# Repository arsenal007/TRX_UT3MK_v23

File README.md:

# TRX_UT3MK_v23
MAINBOARD for UT3MK v23.01

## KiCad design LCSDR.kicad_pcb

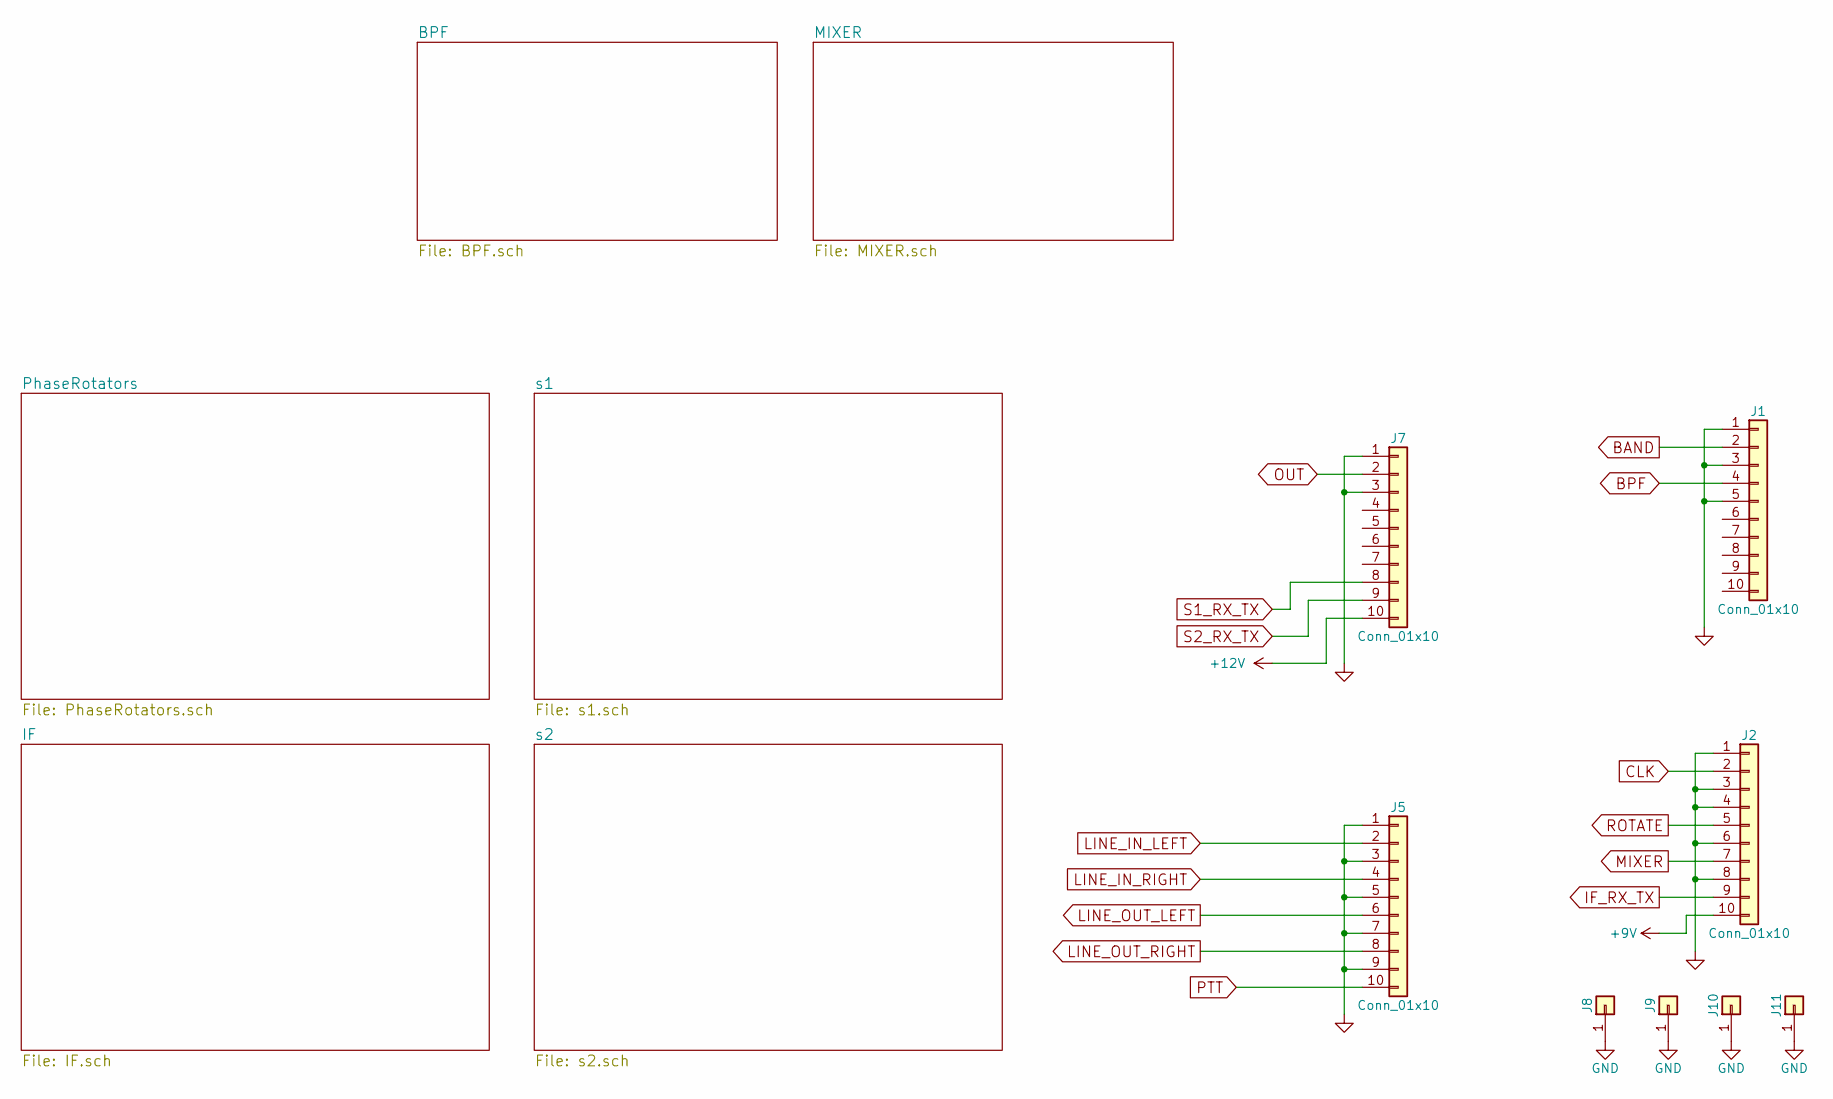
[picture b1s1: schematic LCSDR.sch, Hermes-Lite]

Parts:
J1, J2, J5, J7: Conn_01x10; Pin_Header_Straight_1x10_Pitch2.54mm
J8, J9, J10, J11: Conn_01x01; MountingHole_3.2mm_M3_DIN965_Pad

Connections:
+9V: J2.10; also elsewhere on the board
+12V: J7.10; also elsewhere on the board
BAND: J1.2; also elsewhere on the board
BPF: J1.4; also elsewhere on the board
CLK: J2.2; also elsewhere on the board
GND: J1.1, J1.3, J1.5, J2.1, J2.3, J2.4, J2.6, J2.8, J5.1, J5.3, J5.5, J5.7, J5.9, J7.1, J7.3, J8.1, J9.1, J10.1, J11.1; also elsewhere on the board
IF_RX_TX: J2.9; also elsewhere on the board
LINE_IN_LEFT: J5.2; also elsewhere on the board
LINE_IN_RIGHT: J5.4; also elsewhere on the board
LINE_OUT_LEFT: J5.6; also elsewhere on the board
LINE_OUT_RIGHT: J5.8; also elsewhere on the board
MIXER: J2.7; also elsewhere on the board
OUT: J7.2; also elsewhere on the board
PTT: J5.10; also elsewhere on the board
ROTATE: J2.5; also elsewhere on the board
S1_RX_TX: J7.8; also elsewhere on the board
S2_RX_TX: J7.9; also elsewhere on the board

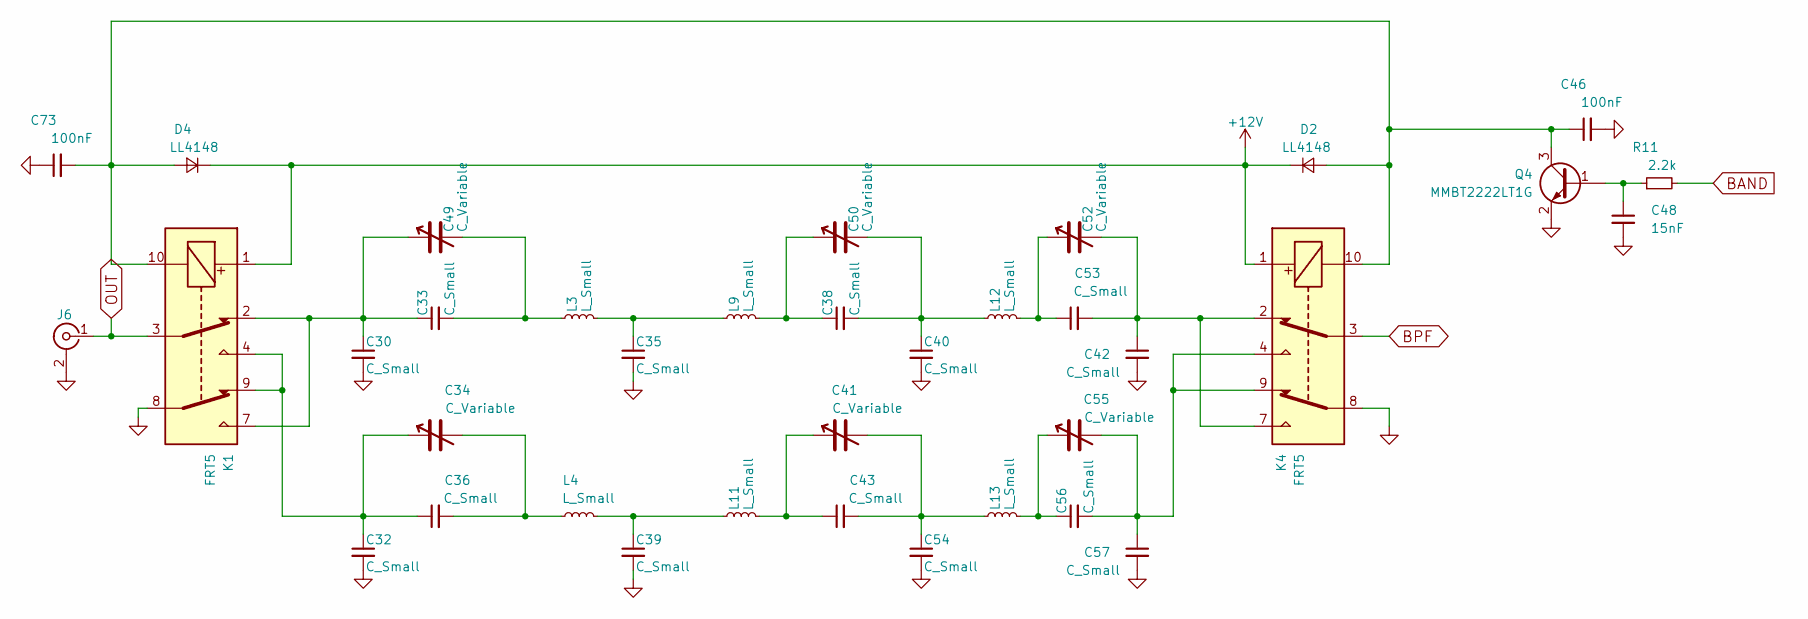
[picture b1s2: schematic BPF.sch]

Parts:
C30, C32, C33, C35, C36, C38, C39, C40, C42, C43, C53, C54, C56, C57: C_Small; C_1206_0603
C34, C41, C49, C50, C52, C55: C_Variable; C_Trimmer_Murata_TZC3
C46, C73: 100nF; C_1206_0603
C48: 15nF; C_0603_HandSoldering
D2, D4: LL4148; D_MiniMELF
J6: Conn_Coaxial; RFCONNECTOR
K1, K4: FRT5; Relay_DPDT_FRT5
L3, L4, L9, L11, L12, L13: L_Small; Choke_Toroid_6,5x13mm_Vertical
Q4: MMBT2222LT1G; SOT-23
R11: 2.2k; R_1206_0603

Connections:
+12V: D2.1 (K), D4.1 (K), K1.1, K4.1; also elsewhere on the board
BAND: R11.2; also elsewhere on the board
BPF: K4.3; also elsewhere on the board
GND: C30.2, C32.2, C35.2, C39.2, C40.2, C42.2, C46.2, C48.2, C54.2, C57.2, C73.1, J6.2 (Ext), K1.8, K4.8, Q4.2 (E); also elsewhere on the board
unnamed: C30.1, C33.1, C49.1, K1.2, K1.7
unnamed: C32.1, C34.1, C36.1, K1.4, K1.9
unnamed: C33.2, C49.2, L3.1
unnamed: C34.2, C36.2, L4.1
unnamed: C35.1, L3.2, L9.1
unnamed: C38.1, C50.1, L9.2
unnamed: C38.2, C40.1, C50.2, L12.1
unnamed: C39.1, L4.2, L11.1
unnamed: C41.1, C43.1, L11.2
unnamed: C41.2, C43.2, C54.1, L13.1
unnamed: C42.1, C52.2, C53.2, K4.2, K4.7
unnamed: C46.1, C73.2, D2.2 (A), D4.2 (A), K1.10, K4.10, Q4.3 (C)
unnamed: C48.1, Q4.1 (B), R11.1
unnamed: C52.1, C53.1, L12.2
unnamed: C55.1, C56.1, L13.2
unnamed: C55.2, C56.2, C57.1, K4.4, K4.9
OUT: J6.1 (In), K1.3; also elsewhere on the board

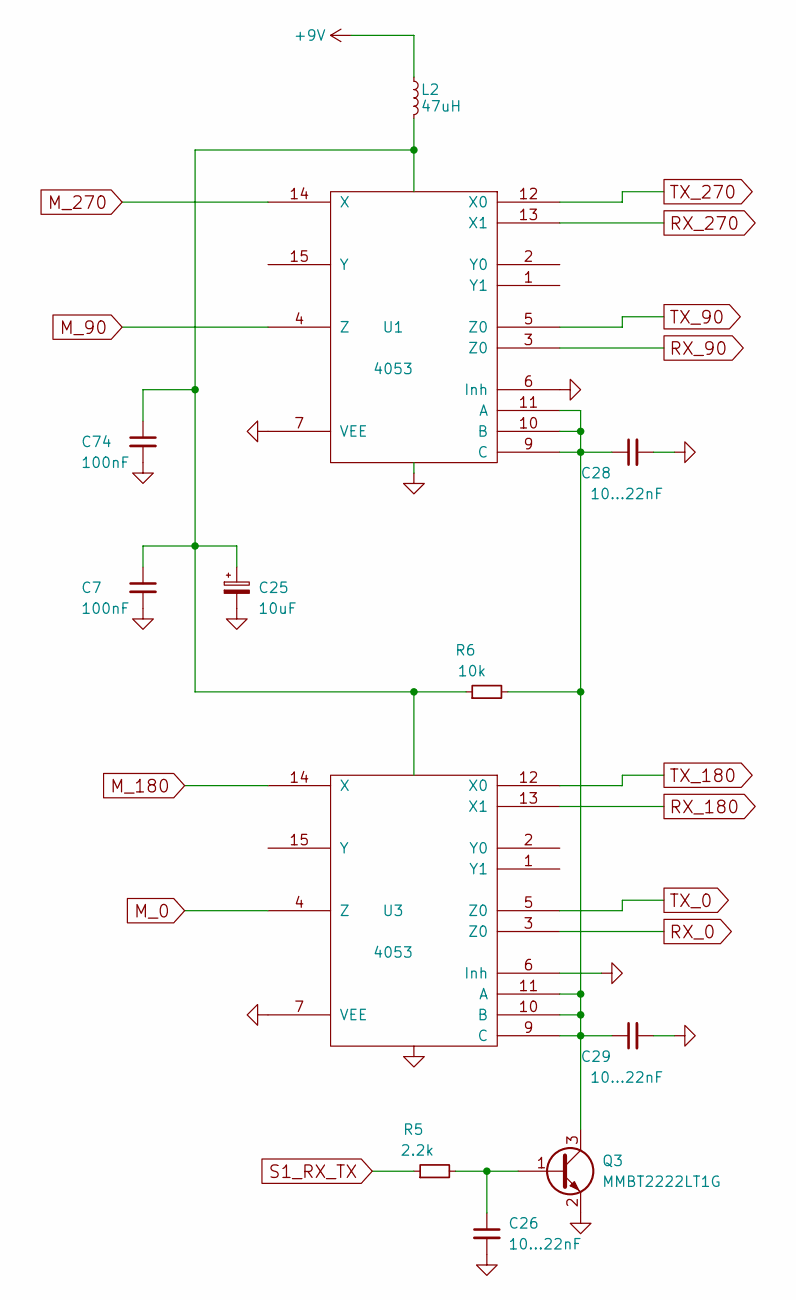
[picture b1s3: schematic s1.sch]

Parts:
C7, C74: 100nF; C_1206_0603
C25: 10uF; CP_Radial_D5.0mm_P2.00mm
C26, C28, C29: 10...22nF; C_0603_HandSoldering
L2: 47uH; Choke_Horizontal_RM10mm
Q3: MMBT2222LT1G; SOT-23
R5: 2.2k; R_1206_0603
R6: 10k; R_0603_HandSoldering
U1, U3: 4053; TSSOP-16_4.4x5mm_Pitch0.65mm

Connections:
+9V: L2.1; also elsewhere on the board
GND: C7.2, C25.2, C26.2, C28.2, C29.2, C74.2, Q3.2 (E), U1.6 (Inh), U1.7 (VEE), U1.8 (VSS), U3.6 (Inh), U3.7 (VEE), U3.8 (VSS); also elsewhere on the board
M_0: U3.4 (Z); also elsewhere on the board
M_90: U1.4 (Z); also elsewhere on the board
M_180: U3.14 (X); also elsewhere on the board
M_270: U1.14 (X); also elsewhere on the board
unnamed: C26.1, Q3.1 (B), R5.2
unnamed: C28.1, C29.1, Q3.3 (C), R6.2, U1.9 (C), U1.10 (B), U1.11 (A), U3.9 (C), U3.10 (B), U3.11 (A)
RX_0: U3.3 (Z0); also elsewhere on the board
RX_90: U1.3 (Z0); also elsewhere on the board
RX_180: U3.13 (X1); also elsewhere on the board
RX_270: U1.13 (X1); also elsewhere on the board
S1_RX_TX: R5.1; also elsewhere on the board
TX_0: U3.5 (Z0); also elsewhere on the board
TX_90: U1.5 (Z0); also elsewhere on the board
TX_180: U3.12 (X0); also elsewhere on the board
TX_270: U1.12 (X0); also elsewhere on the board
VDD: C7.1, C25.1, C74.1, L2.2, R6.1, U1.16 (VDD), U3.16 (VDD)

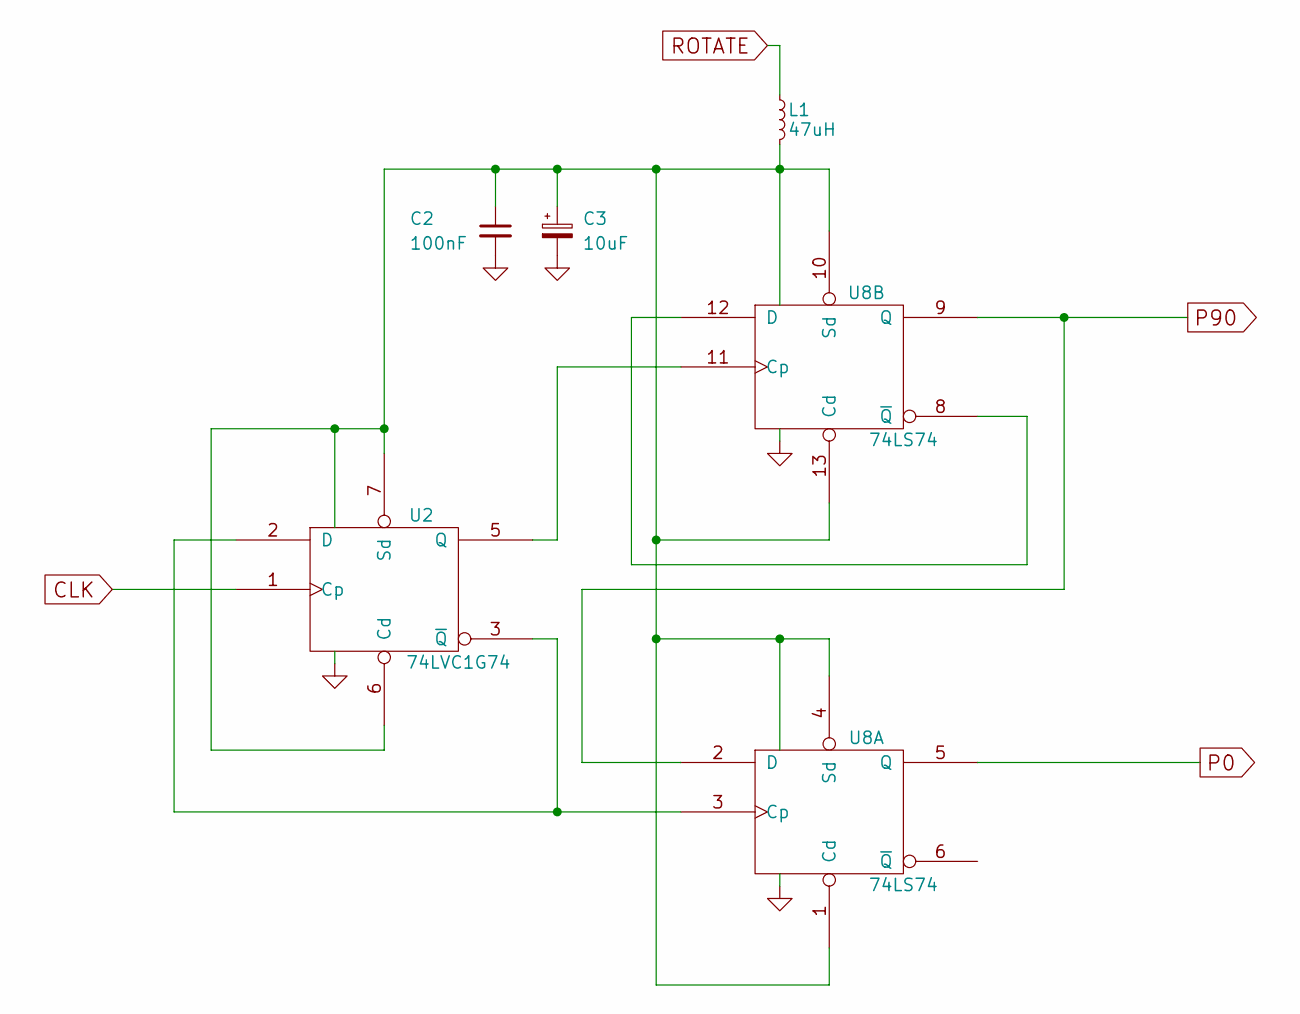
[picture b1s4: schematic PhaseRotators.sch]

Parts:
C2: 100nF; C_1206_0603
C3: 10uF; CP_Radial_D5.0mm_P2.00mm
L1: 47uH; Choke_Horizontal_RM10mm
U2: 74LVC1G74; TSSOP-8_3x3mm_Pitch0.65mm
U8: 74LS74; TSSOP-14_4.4x5mm_Pitch0.65mm

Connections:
CLK: U2.1 (Cp); also elsewhere on the board
GND: C2.2, C3.2, U2.4 (GND), U8.7 (GND); also elsewhere on the board
unnamed: U2.2 (D), U2.3 (~Q), U8.3 (Cp)
unnamed: U2.5 (Q), U8.11 (Cp)
unnamed: U8.8 (~Q), U8.12 (D)
P0: U8.5 (Q); also elsewhere on the board
P90: U8.2 (D), U8.9 (Q); also elsewhere on the board
ROTATE: L1.1; also elsewhere on the board
VCC: C2.1, C3.1, L1.2, U2.6 (Cd), U2.7 (Sd), U2.8 (VCC), U8.1 (Cd), U8.4 (Sd), U8.10 (Sd), U8.13 (Cd), U8.14 (VCC)

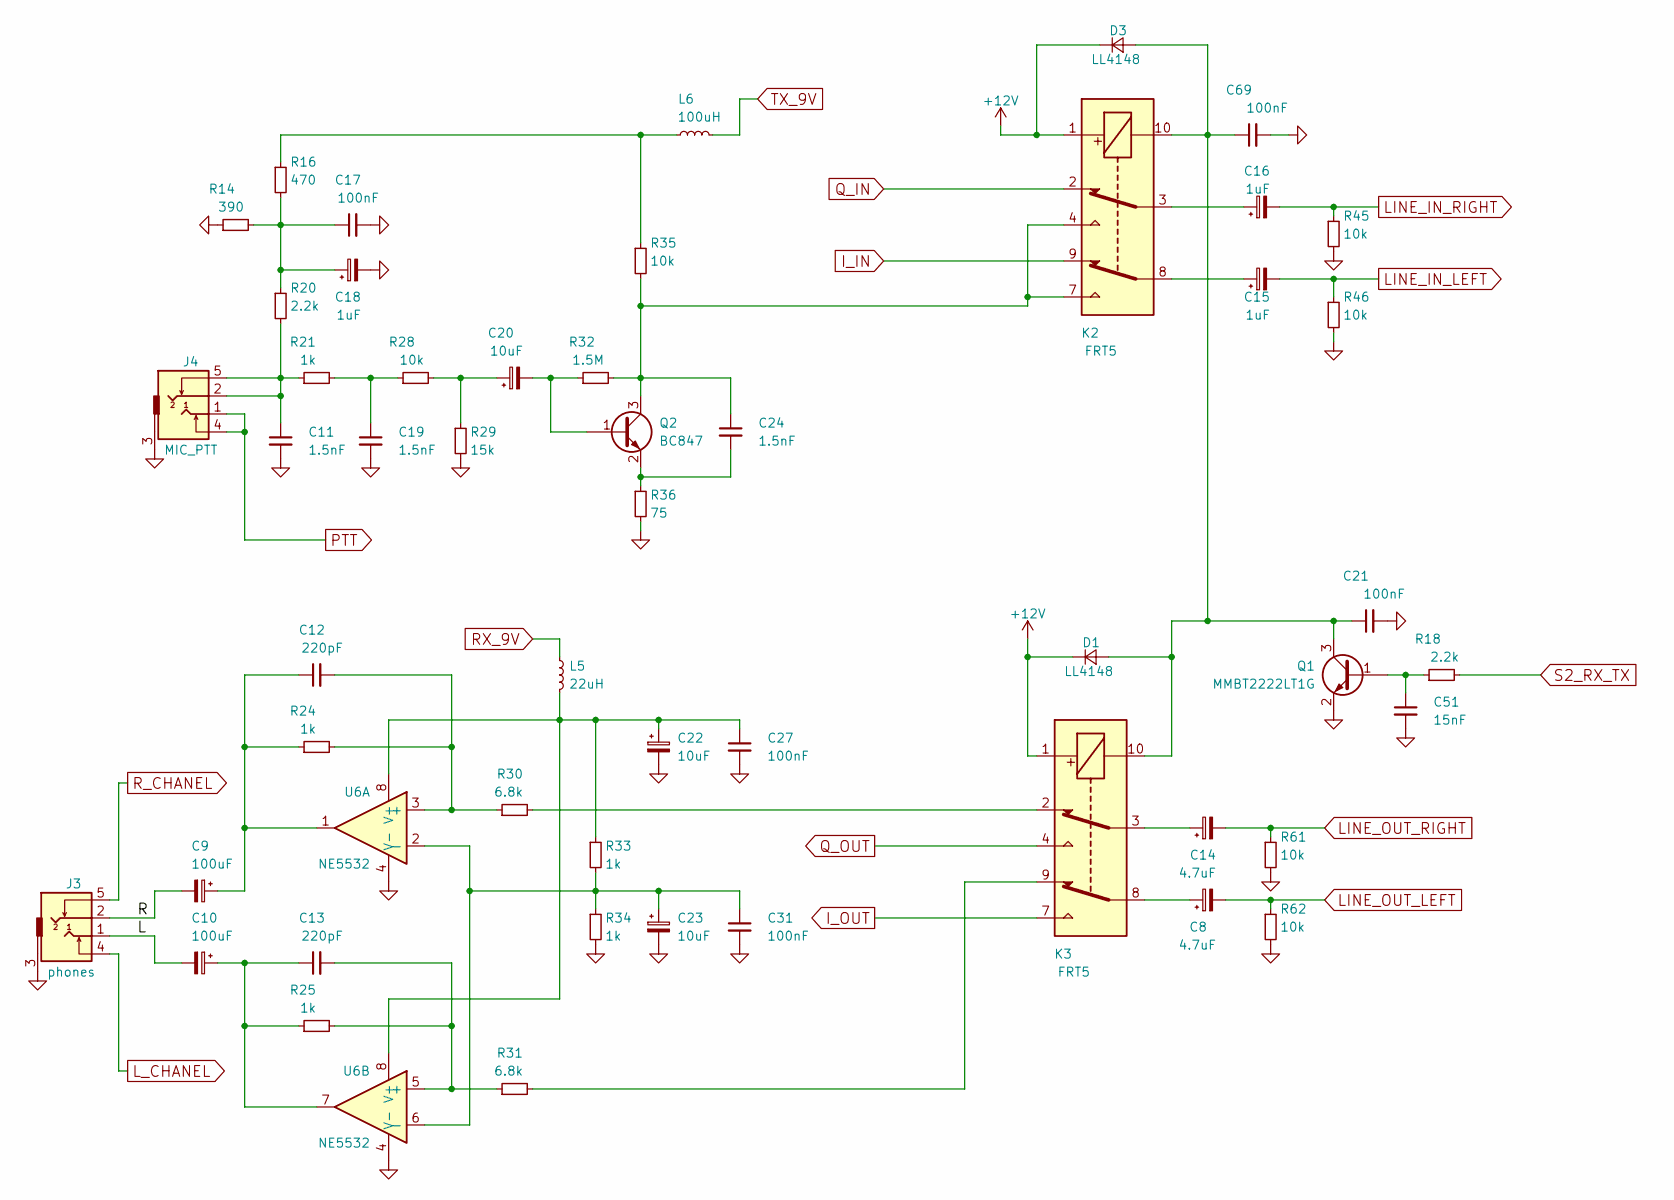
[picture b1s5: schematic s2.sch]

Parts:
C8, C14: 4.7uF; CP_Radial_D5.0mm_P2.00mm
C9, C10: 100uF; CP_Radial_D6.3mm_P2.50mm
C11, C19, C24: 1.5nF; C_1206_0603
C12, C13: 220pF; C_1206_0603
C15, C16, C18: 1uF; CP_Radial_D5.0mm_P2.00mm
C17, C21, C27, C31, C69: 100nF; C_1206_0603
C20, C22, C23: 10uF; CP_Radial_D5.0mm_P2.00mm
C51: 15nF; C_0603_HandSoldering
D1, D3: LL4148; D_MiniMELF
J3: phones; audio_jack_3_5mm_PJ307
J4: MIC_PTT; audio_jack_3_5mm_PJ307
K2, K3: FRT5; Relay_DPDT_FRT5
L5: 22uH; Choke_Horizontal_RM10mm
L6: 100uH; Choke_Horizontal_RM10mm
Q1: MMBT2222LT1G; SOT-23
Q2: BC847; SOT-23
R14: 390; R_1206_0603
R16: 470; R_1206_0603
R18, R20: 2.2k; R_1206_0603
R21, R24, R25, R33, R34: 1k; R_1206_0603
R28, R35, R45, R46, R61, R62: 10k; R_1206_0603
R29: 15k; R_1206_0603
R30, R31: 6.8k; R_1206_0603
R32: 1.5M; R_1206_0603
R36: 75; R_1206_0603
U6: NE5532; SOIC-8_3.9x4.9mm_Pitch1.27mm

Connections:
+12V: D1.1 (K), D3.1 (K), K2.1, K3.1; also elsewhere on the board
/s2/L: C10.2, J3.1
/s2/R: C9.2, J3.2
GND: C11.2, C17.2, C18.2, C19.2, C21.2, C22.2, C23.2, C27.2, C31.2, C51.2, C69.2, J3.3, J4.3, Q1.2 (E), R14.1, R29.2, R34.2, R36.2, R45.2, R46.2, R61.2, R62.2, U6.4 (V-); also elsewhere on the board
I_IN: K2.9; also elsewhere on the board
I_OUT: K3.7; also elsewhere on the board
LINE_IN_LEFT: C15.2, R46.1; also elsewhere on the board
LINE_IN_RIGHT: C16.2, R45.1; also elsewhere on the board
LINE_OUT_LEFT: C8.2, R62.1; also elsewhere on the board
LINE_OUT_RIGHT: C14.2, R61.1; also elsewhere on the board
unnamed: C8.1, K3.8
unnamed: C10.1, C13.1, R25.1, U6.7
unnamed: C11.1, J4.2, J4.5, R20.2, R21.1
unnamed: C9.1, C12.1, R24.1, U6.1
unnamed: C12.2, R24.2, R30.1, U6.3 (+)
unnamed: C13.2, R25.2, R31.1, U6.5 (+)
unnamed: C14.1, K3.3
unnamed: C15.1, K2.8
unnamed: C16.1, K2.3
unnamed: C17.1, C18.1, R14.2, R16.2, R20.1
unnamed: C19.1, R21.2, R28.1
unnamed: C20.1, R28.2, R29.1
unnamed: C20.2, Q2.1 (B), R32.1
unnamed: C21.1, C69.1, D1.2 (A), D3.2 (A), K2.10, K3.10, Q1.3 (C)
unnamed: C22.1, C27.1, L5.2, R33.1, U6.8 (V+)
unnamed: C23.1, C31.1, R33.2, R34.1, U6.2 (-), U6.6 (-)
unnamed: C24.1, K2.4, K2.7, Q2.3 (C), R32.2, R35.2
unnamed: C24.2, Q2.2 (E), R36.1
unnamed: C51.1, Q1.1 (B), R18.1
unnamed: K3.2, R30.2
unnamed: K3.9, R31.2
unnamed: L6.1, R16.1, R35.1
PTT: J4.1, J4.4; also elsewhere on the board
Q_IN: K2.2; also elsewhere on the board
Q_OUT: K3.4; also elsewhere on the board
RX_9V: L5.1; also elsewhere on the board
S2_RX_TX: R18.2; also elsewhere on the board
TX_9V: L6.2; also elsewhere on the board

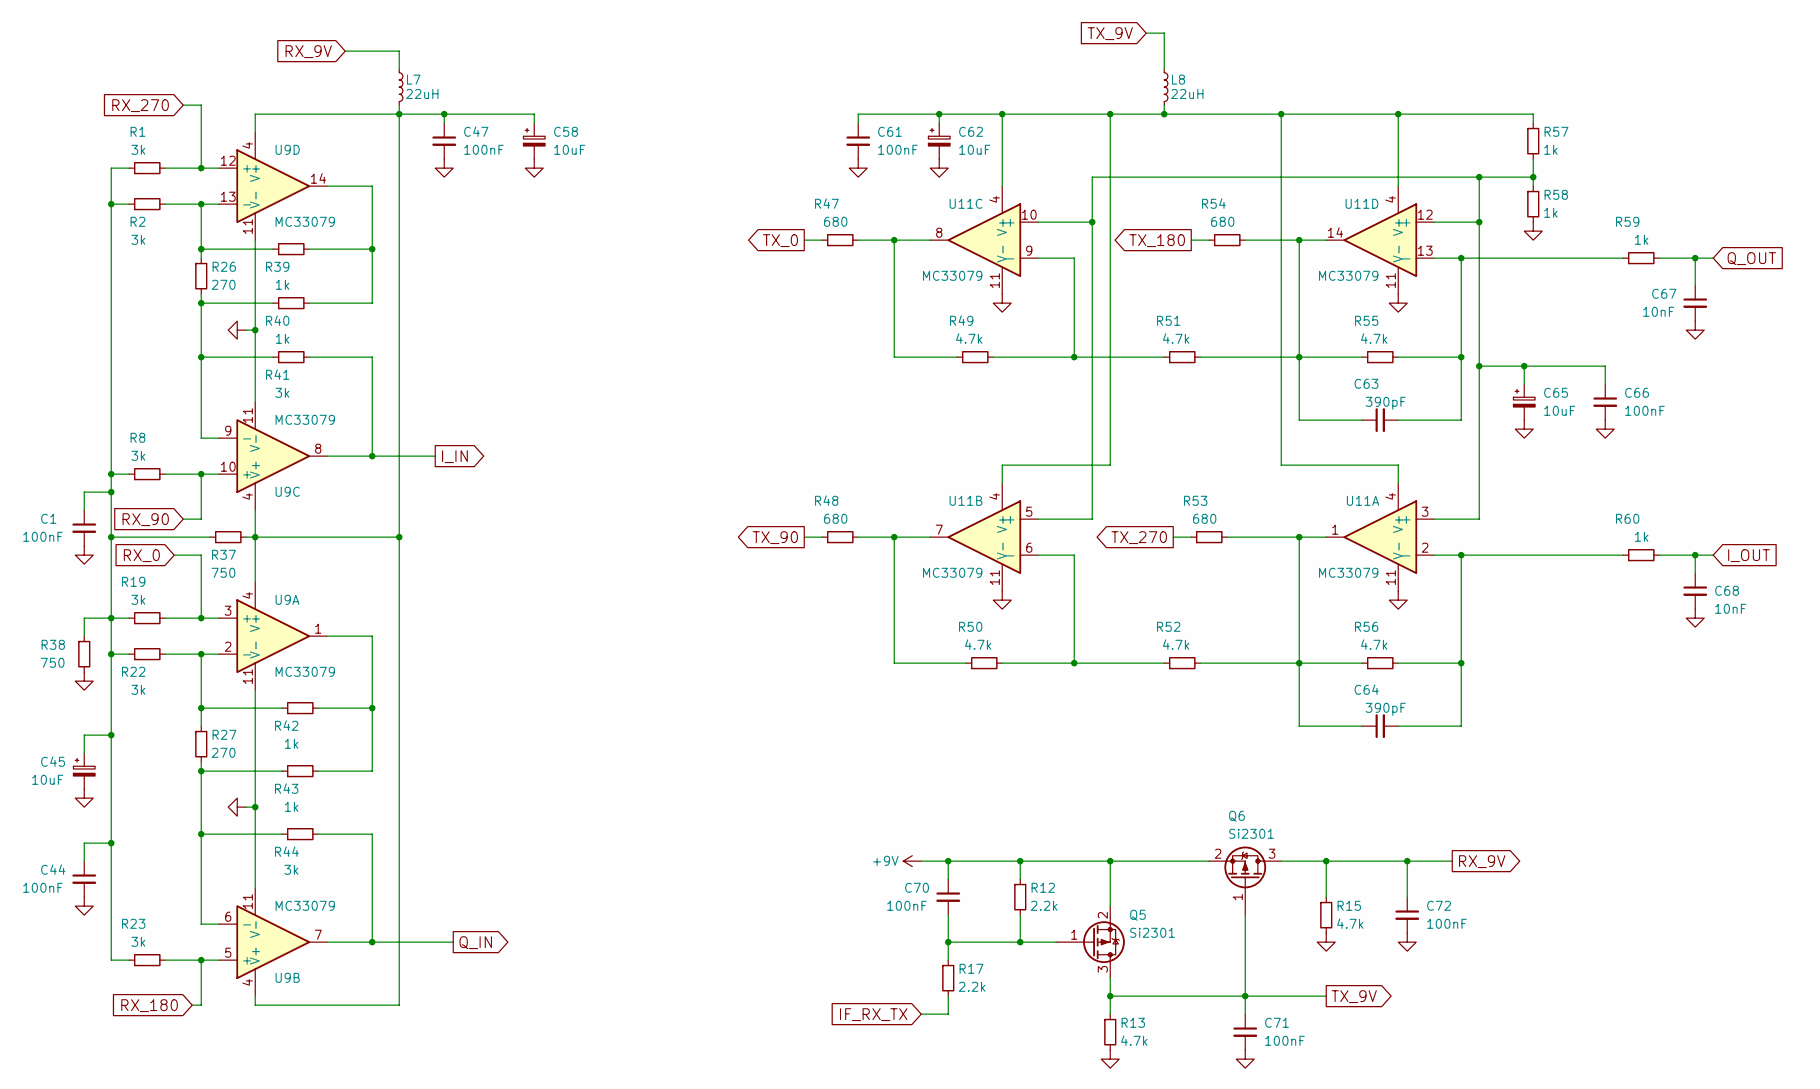
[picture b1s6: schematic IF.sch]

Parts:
C1, C44, C47, C61, C66, C70, C71, C72: 100nF; C_1206_0603
C45, C58, C62, C65: 10uF; CP_Radial_D5.0mm_P2.00mm
C63, C64: 390pF; C_0603_HandSoldering
C67, C68: 10nF; C_0603_HandSoldering
L7: 22uH; Choke_Horizontal_RM10mm
L8: 22uH; Choke_Horizontal_RM15mm
Q5, Q6: Si2301; SOT-23
R1, R2, R8, R19, R22, R23, R41, R44: 3k; R_0603_HandSoldering
R12, R17: 2.2k; R_1206_0603
R13, R15: 4.7k; R_1206_0603
R26, R27: 270; R_0603_HandSoldering
R37, R38: 750; R_1206_0603
R39, R40, R42, R43, R59, R60: 1k; R_0603_HandSoldering
R47, R48, R53, R54: 680; R_0603_HandSoldering
R49, R50, R51, R52, R55, R56: 4.7k; R_0603_HandSoldering
R57, R58: 1k; R_1206_0603
U9, U11: MC33079; SOIC-14_3.9x8.7mm_Pitch1.27mm

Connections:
+9V: C70.1, Q5.2 (S), Q6.2 (S), R12.1; also elsewhere on the board
GND: C1.2, C44.2, C45.2, C47.2, C58.2, C61.2, C62.2, C65.2, C66.2, C67.2, C68.2, C71.2, C72.2, R13.2, R15.2, R38.2, R58.2, U9.11 (V-), U11.11 (V-); also elsewhere on the board
IF_RX_TX: R17.2; also elsewhere on the board
I_IN: R41.2, U9.8; also elsewhere on the board
I_OUT: C68.1, R60.2; also elsewhere on the board
unnamed: C1.1, C44.1, C45.1, R1.1, R2.1, R8.1, R19.1, R22.1, R23.1, R37.1, R38.1
unnamed: C47.1, C58.1, L7.2, R37.2, U9.4 (V+)
unnamed: C61.1, C62.1, L8.2, R57.1, U11.4 (V+)
unnamed: C63.1, R51.2, R54.2, R55.1, U11.14
unnamed: C63.2, R55.2, R59.1, U11.13 (-)
unnamed: C64.1, R52.2, R53.2, R56.1, U11.1
unnamed: C64.2, R56.2, R60.1, U11.2 (-)
unnamed: C65.1, C66.1, R57.2, R58.1, U11.3 (+), U11.5 (+), U11.10 (+), U11.12 (+)
unnamed: C70.2, Q5.1 (G), R12.2, R17.1
unnamed: R2.2, R26.1, R39.1, U9.13 (-)
unnamed: R22.2, R27.1, R42.1, U9.2 (-)
unnamed: R26.2, R40.1, R41.1, U9.9 (-)
unnamed: R27.2, R43.1, R44.1, U9.6 (-)
unnamed: R39.2, R40.2, U9.14
unnamed: R42.2, R43.2, U9.1
unnamed: R47.2, R49.1, U11.8
unnamed: R48.2, R50.1, U11.7
unnamed: R49.2, R51.1, U11.9 (-)
unnamed: R50.2, R52.1, U11.6 (-)
Q_IN: R44.2, U9.7; also elsewhere on the board
Q_OUT: C67.1, R59.2; also elsewhere on the board
RX_0: R19.2, U9.3 (+); also elsewhere on the board
RX_9V: C72.1, L7.1, Q6.3 (D), R15.1; also elsewhere on the board
RX_90: R8.2, U9.10 (+); also elsewhere on the board
RX_180: R23.2, U9.5 (+); also elsewhere on the board
RX_270: R1.2, U9.12 (+); also elsewhere on the board
TX_0: R47.1; also elsewhere on the board
TX_9V: C71.1, L8.1, Q5.3 (D), Q6.1 (G), R13.1; also elsewhere on the board
TX_90: R48.1; also elsewhere on the board
TX_180: R54.1; also elsewhere on the board
TX_270: R53.1; also elsewhere on the board

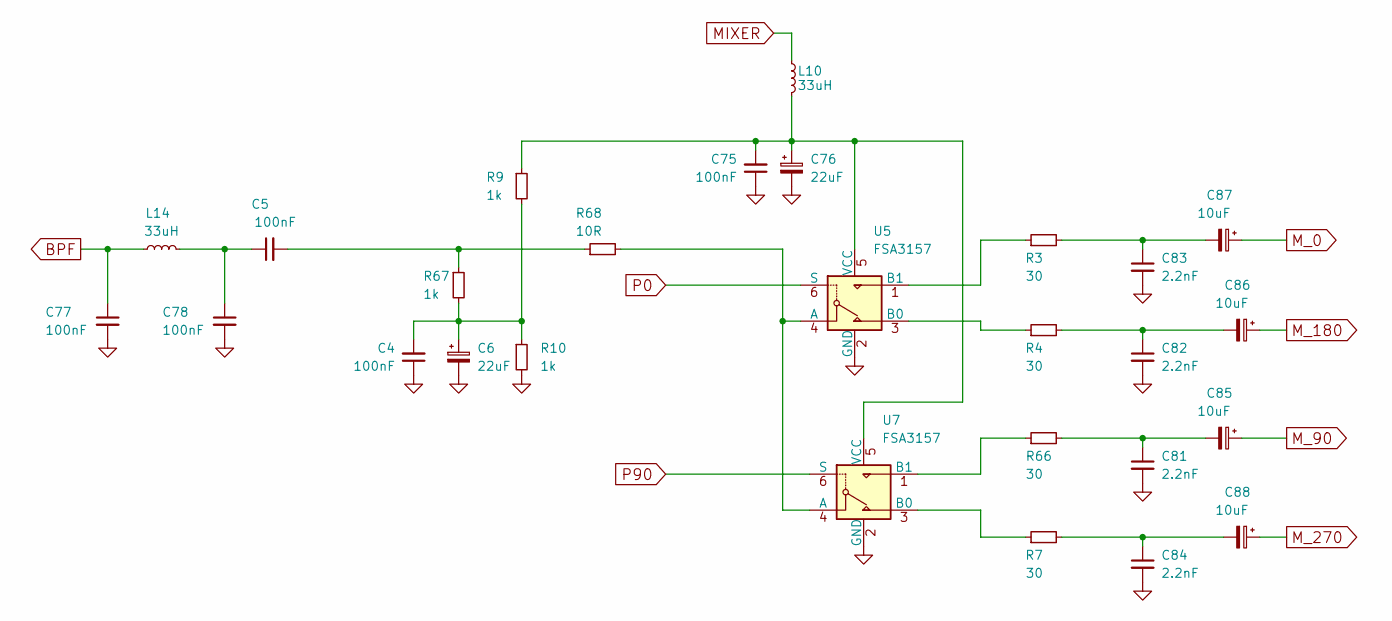
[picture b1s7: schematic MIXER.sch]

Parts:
C4, C75: 100nF; C_1206_0603
C5, C77, C78: 100nF; C_Disc_D7.0mm_W2.5mm_P5.00mm
C6, C76: 22uF; CP_Radial_D5.0mm_P2.00mm
C81, C82, C83, C84: 2.2nF; C_1206_0603
C85, C86, C87, C88: 10uF; CP_Tantalum_Case-A_EIA-3216-18_Wave
L10, L14: 33uH; Choke_Horizontal_RM10mm
R3, R4, R7, R66: 30; R_1206_0603
R9, R10, R67: 1k; R_1206_0603
R68: 10R; R_1206_0603
U5, U7: FSA3157; SOT-23-6

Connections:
BPF: C77.1, L14.1; also elsewhere on the board
GND: C4.1, C6.2, C75.1, C76.2, C77.2, C78.2, C81.2, C82.2, C83.2, C84.2, R10.2, U5.2 (GND), U7.2 (GND); also elsewhere on the board
MIXER: L10.1; also elsewhere on the board
M_0: C87.1; also elsewhere on the board
M_90: C85.1; also elsewhere on the board
M_180: C86.1; also elsewhere on the board
M_270: C88.1; also elsewhere on the board
unnamed: C4.2, C6.1, R9.2, R10.1, R67.2
unnamed: C5.1, C78.1, L14.2
unnamed: C5.2, R67.1, R68.1
unnamed: C75.2, C76.1, L10.2, R9.1, U5.5 (VCC), U7.5 (VCC)
unnamed: C81.1, C85.2, R66.2
unnamed: C82.1, C86.2, R4.2
unnamed: C83.1, C87.2, R3.2
unnamed: C84.1, C88.2, R7.2
unnamed: R3.1, U5.1 (B1)
unnamed: R4.1, U5.3 (B0)
unnamed: R7.1, U7.3 (B0)
unnamed: R66.1, U7.1 (B1)
unnamed: R68.2, U5.4 (A), U7.4 (A)
P0: U5.6 (S); also elsewhere on the board
P90: U7.6 (S); also elsewhere on the board

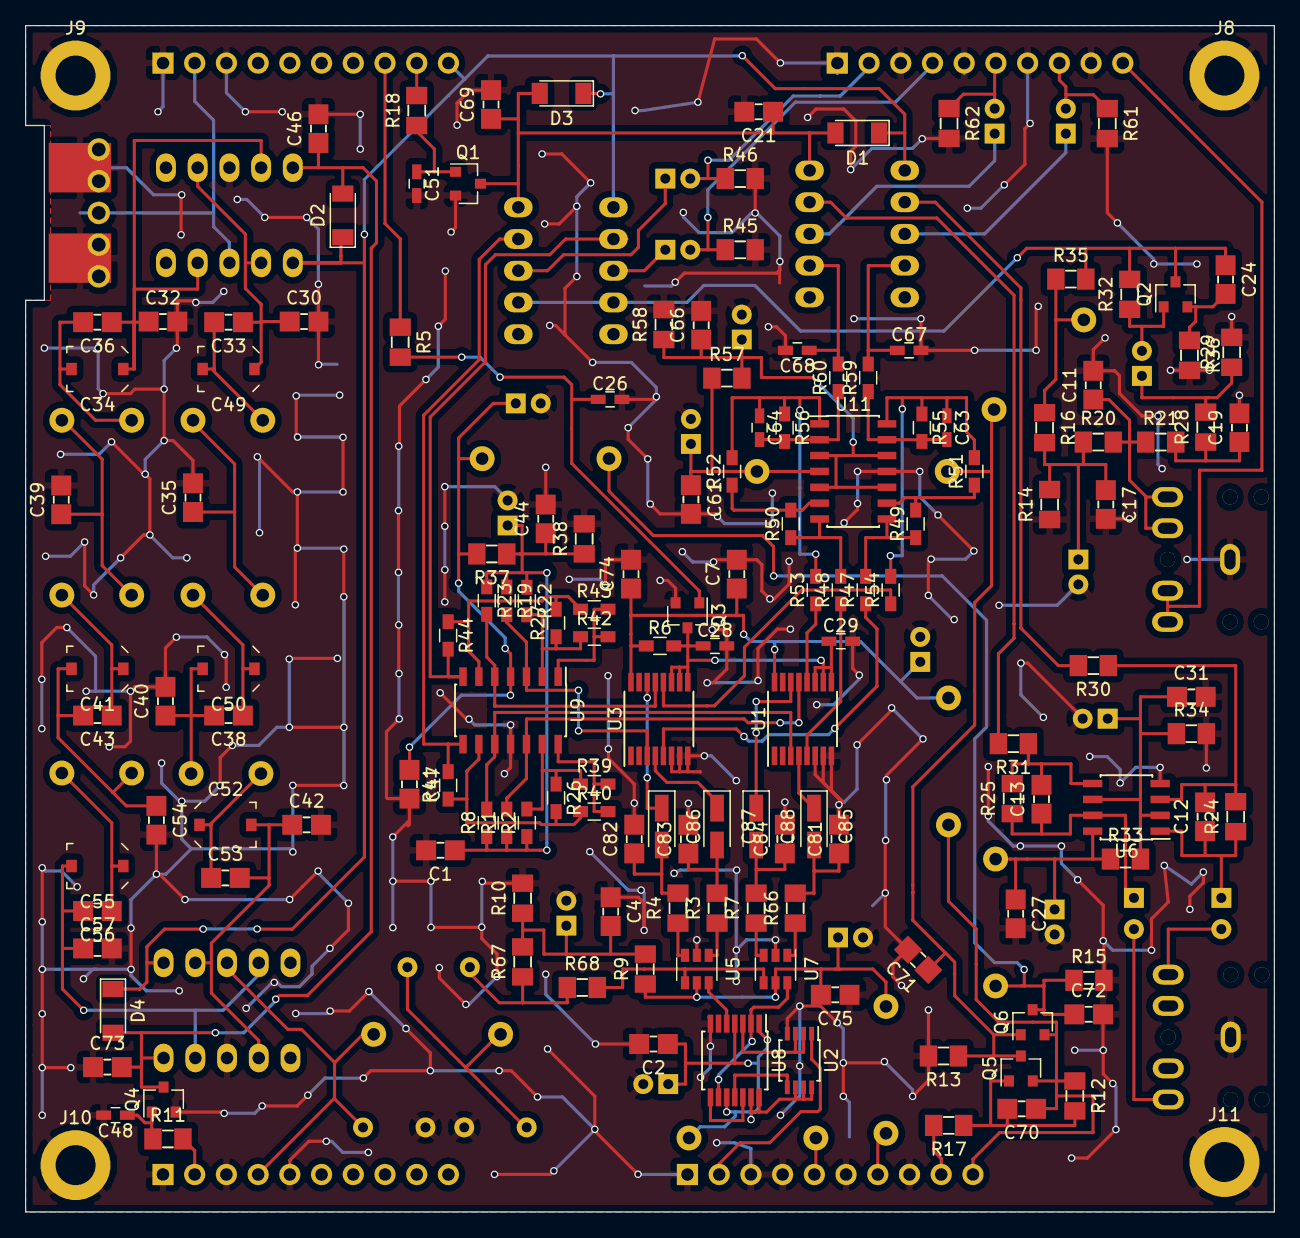
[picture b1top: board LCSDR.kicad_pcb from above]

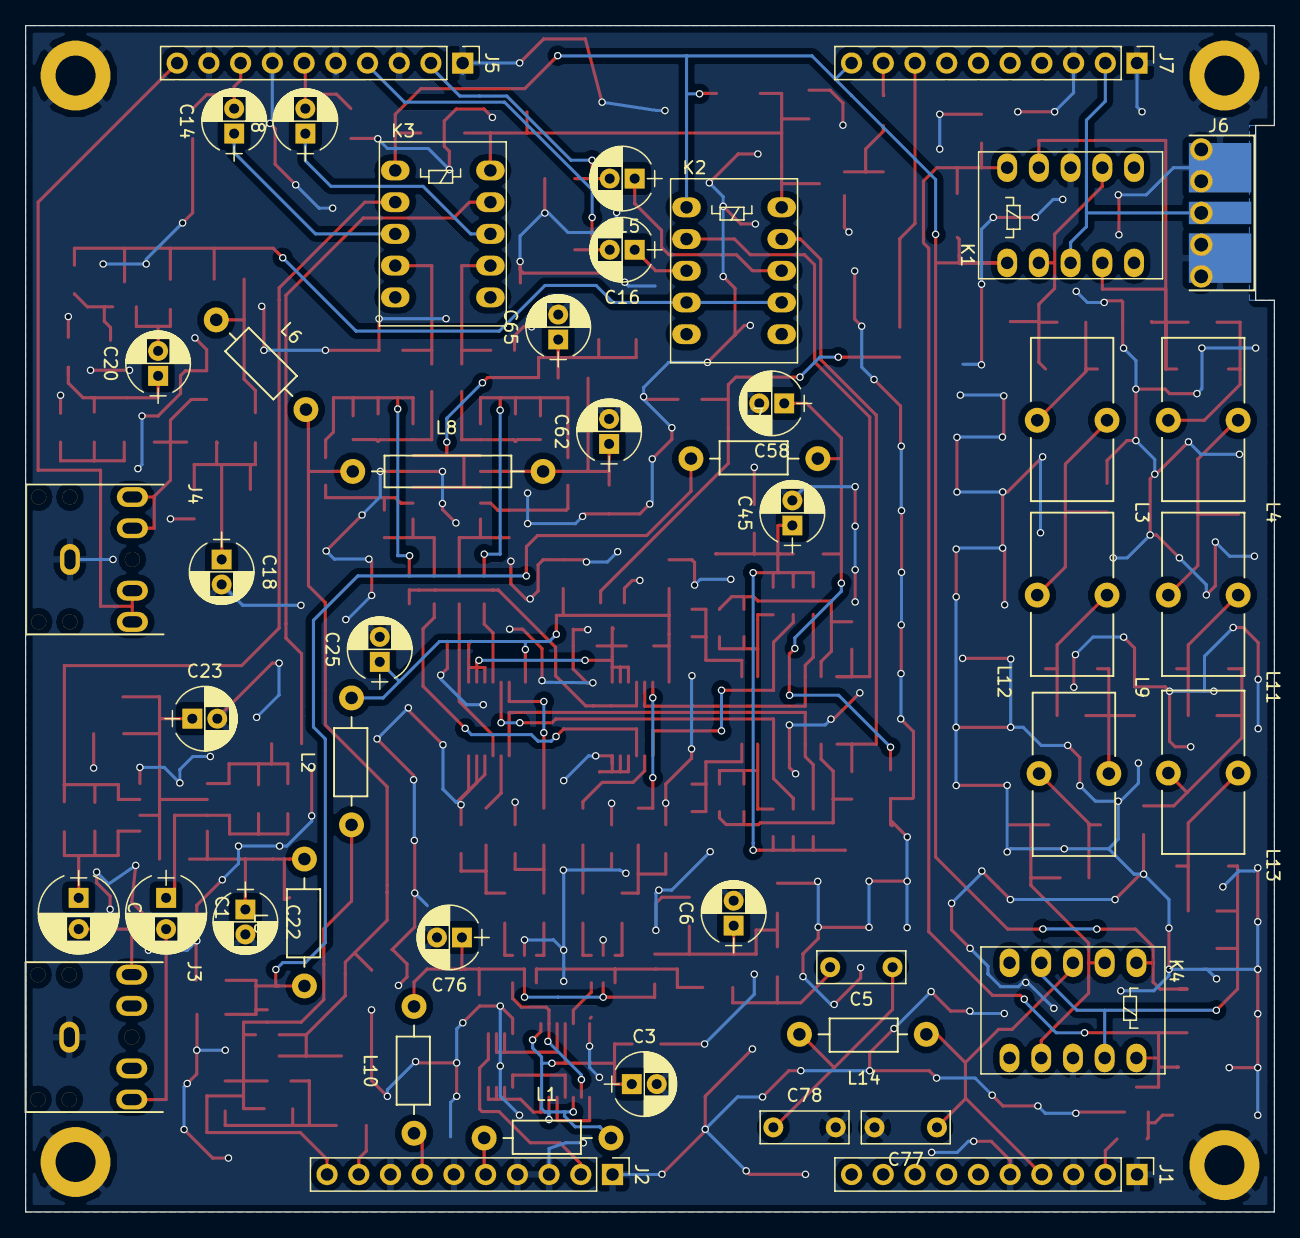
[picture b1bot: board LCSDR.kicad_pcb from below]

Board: 2 copper layers, 100.0 x 95.0 mm, 196 parts (46 on the bottom side), 116 nets.

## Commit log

2020-05-04 first edit
2020-05-05 rotators 2 74lvc1G74
2020-05-05 PCB s1
2020-05-13 need some GND vias
2020-05-13 rm MIXERS
2020-05-14 production
2020-05-30 Phase shift with 74LCX574 TSSOP-20
2020-06-03 instrumental amplifier in IF
2020-06-06 PCB 74LCX574
2020-06-06 gerber files
2020-06-08 fix PCB distance, right after mixer
2020-06-09 rotate phase with 74LVC74APW
2020-07-06 add gnd vias
